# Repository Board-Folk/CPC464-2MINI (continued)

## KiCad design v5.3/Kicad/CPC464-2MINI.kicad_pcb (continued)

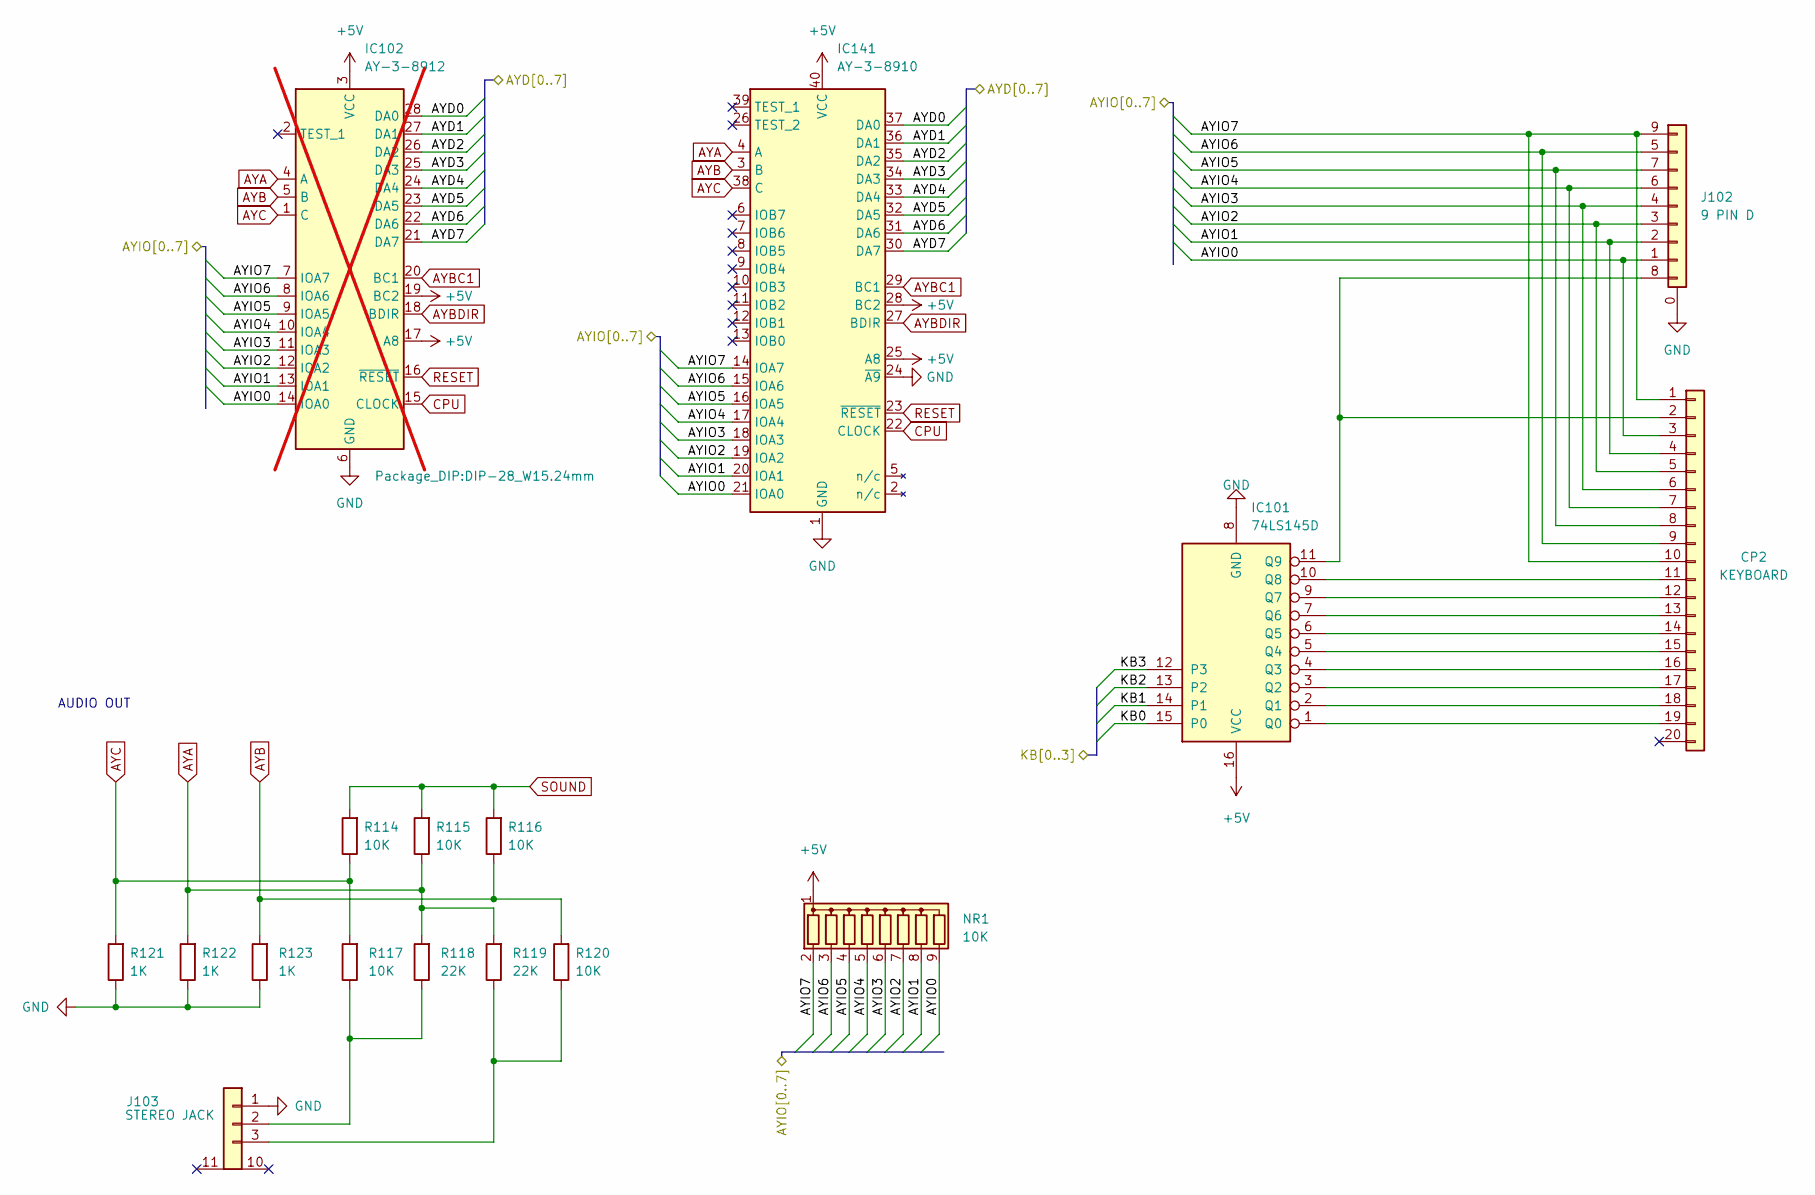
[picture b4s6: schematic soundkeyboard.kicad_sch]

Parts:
CP2: KEYBOARD; PinHeader_1x20_P2.54mm_Vertical
IC101: 74LS145D; SOIC-16_3.9x9.9mm_P1.27mm
IC102: AY-3-8912; DIP-28_W15.24mm; not fitted
IC141: AY-3-8910; DIP-40_W15.24mm
J102: 9 PIN D; DSUB-9_Male_Horizontal_P2.77x2.84mm_EdgePinOffset7.70mm_Hou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
J103: STEREO JACK; STEREO
NR1: 10K; R_Array_SIP9
R114, R115, R116, R117, R120: 10K; R_0805_2012Metric; LCSC C84376
R118, R119: 22K; R_0805_2012Metric; LCSC C114565
R121, R122, R123: 1K; R_0805_2012Metric; LCSC C482939

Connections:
+5V: IC101.16 (VCC), IC102.3 (VCC), IC102.17 (A8), IC102.19 (BC2), IC141.25 (A8), IC141.28 (BC2), IC141.40 (VCC), NR1.1 (common); also elsewhere on the board
/IO/AYD0: IC102.28 (DA0), IC141.37 (DA0); also elsewhere on the board
/IO/AYD1: IC102.27 (DA1), IC141.36 (DA1); also elsewhere on the board
/IO/AYD2: IC102.26 (DA2), IC141.35 (DA2); also elsewhere on the board
/IO/AYD3: IC102.25 (DA3), IC141.34 (DA3); also elsewhere on the board
/IO/AYD4: IC102.24 (DA4), IC141.33 (DA4); also elsewhere on the board
/IO/AYD5: IC102.23 (DA5), IC141.32 (DA5); also elsewhere on the board
/IO/AYD6: IC102.22 (DA6), IC141.31 (DA6); also elsewhere on the board
/IO/AYD7: IC102.21 (DA7), IC141.30 (DA7); also elsewhere on the board
/IO/KB0: IC101.15 (P0); also elsewhere on the board
/IO/KB1: IC101.14 (P1); also elsewhere on the board
/IO/KB2: IC101.13 (P2); also elsewhere on the board
/IO/KB3: IC101.12 (P3); also elsewhere on the board
/Sound & Keyboard/AYIO0: CP2.3, IC102.14 (IOA0), IC141.21 (IOA0), J102.1, NR1.9 (R8)
/Sound & Keyboard/AYIO1: CP2.4, IC102.13 (IOA1), IC141.20 (IOA1), J102.2, NR1.8 (R7)
/Sound & Keyboard/AYIO2: CP2.5, IC102.12 (IOA2), IC141.19 (IOA2), J102.3, NR1.7 (R6)
/Sound & Keyboard/AYIO3: CP2.6, IC102.11 (IOA3), IC141.18 (IOA3), J102.4, NR1.6 (R5)
/Sound & Keyboard/AYIO4: CP2.7, IC102.10 (IOA4), IC141.17 (IOA4), J102.6, NR1.5 (R4)
/Sound & Keyboard/AYIO5: CP2.8, IC102.9 (IOA5), IC141.16 (IOA5), J102.7, NR1.4 (R3)
/Sound & Keyboard/AYIO6: CP2.9, IC102.8 (IOA6), IC141.15 (IOA6), J102.5, NR1.3 (R2)
/Sound & Keyboard/AYIO7: CP2.1, CP2.10, IC102.7 (IOA7), IC141.14 (IOA7), J102.9, NR1.2 (R1)
AYA: IC102.4 (A), IC141.4 (A), R115.1, R118.2, R119.2, R122.2
AYB: IC102.5 (B), IC141.3 (B), R116.1, R120.2, R123.2
AYBC1: IC102.20 (BC1), IC141.29 (BC1); also elsewhere on the board
AYBDIR: IC102.18 (BDIR), IC141.27 (BDIR); also elsewhere on the board
AYC: IC102.1 (C), IC141.38 (C), R114.1, R117.2, R121.2
CPU: IC102.15 (CLOCK), IC141.22 (CLOCK); also elsewhere on the board
GND: IC101.8 (GND), IC102.6 (GND), IC141.1 (GND), IC141.24 (~A9), J102.0 (GND), J103.1, R121.1, R122.1, R123.1; also elsewhere on the board
unnamed: CP2.2, IC101.11 (Q9), J102.8
unnamed: CP2.11, IC101.10 (Q8)
unnamed: CP2.12, IC101.9 (Q7)
unnamed: CP2.13, IC101.7 (Q6)
unnamed: CP2.14, IC101.6 (Q5)
unnamed: CP2.15, IC101.5 (Q4)
unnamed: CP2.16, IC101.4 (Q3)
unnamed: CP2.17, IC101.3 (Q2)
unnamed: CP2.18, IC101.2 (Q1)
unnamed: CP2.19, IC101.1 (Q0)
unnamed: J103.3 (Ground), R119.1, R120.1
unnamed: J103.2, R117.1, R118.1
RESET: IC102.16 (~RESET), IC141.23 (~RESET); also elsewhere on the board
SOUND: R114.2, R115.2, R116.2; also elsewhere on the board

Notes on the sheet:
AUDIO OUT

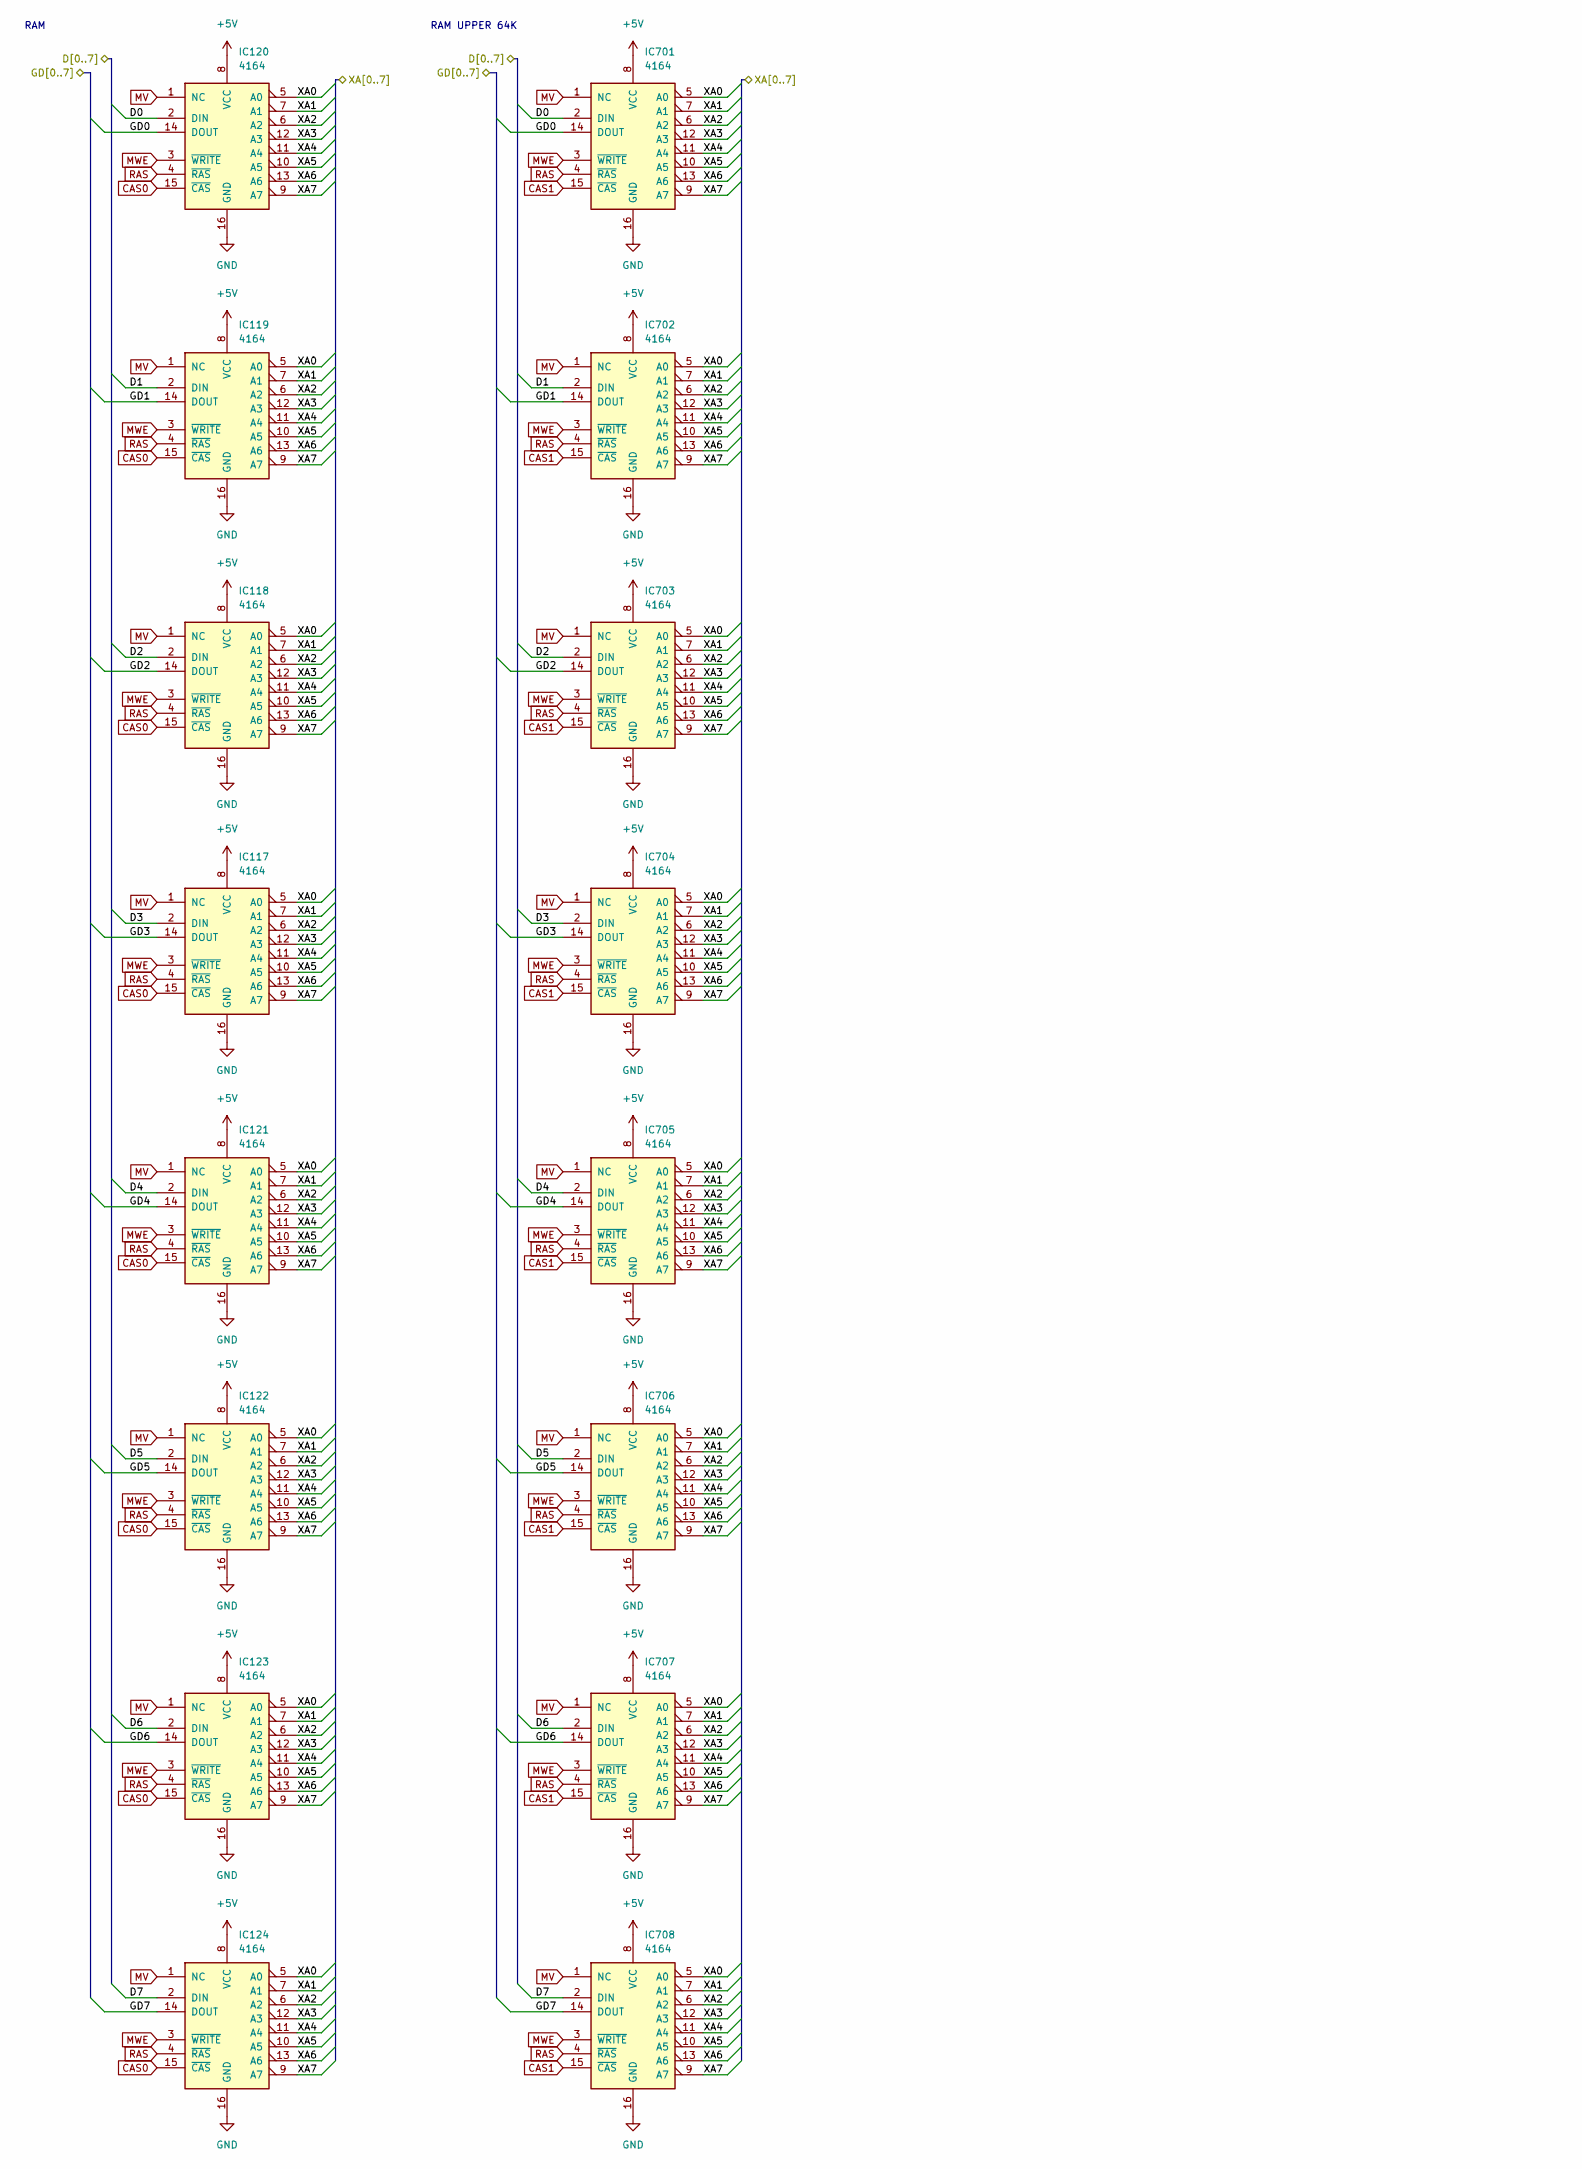
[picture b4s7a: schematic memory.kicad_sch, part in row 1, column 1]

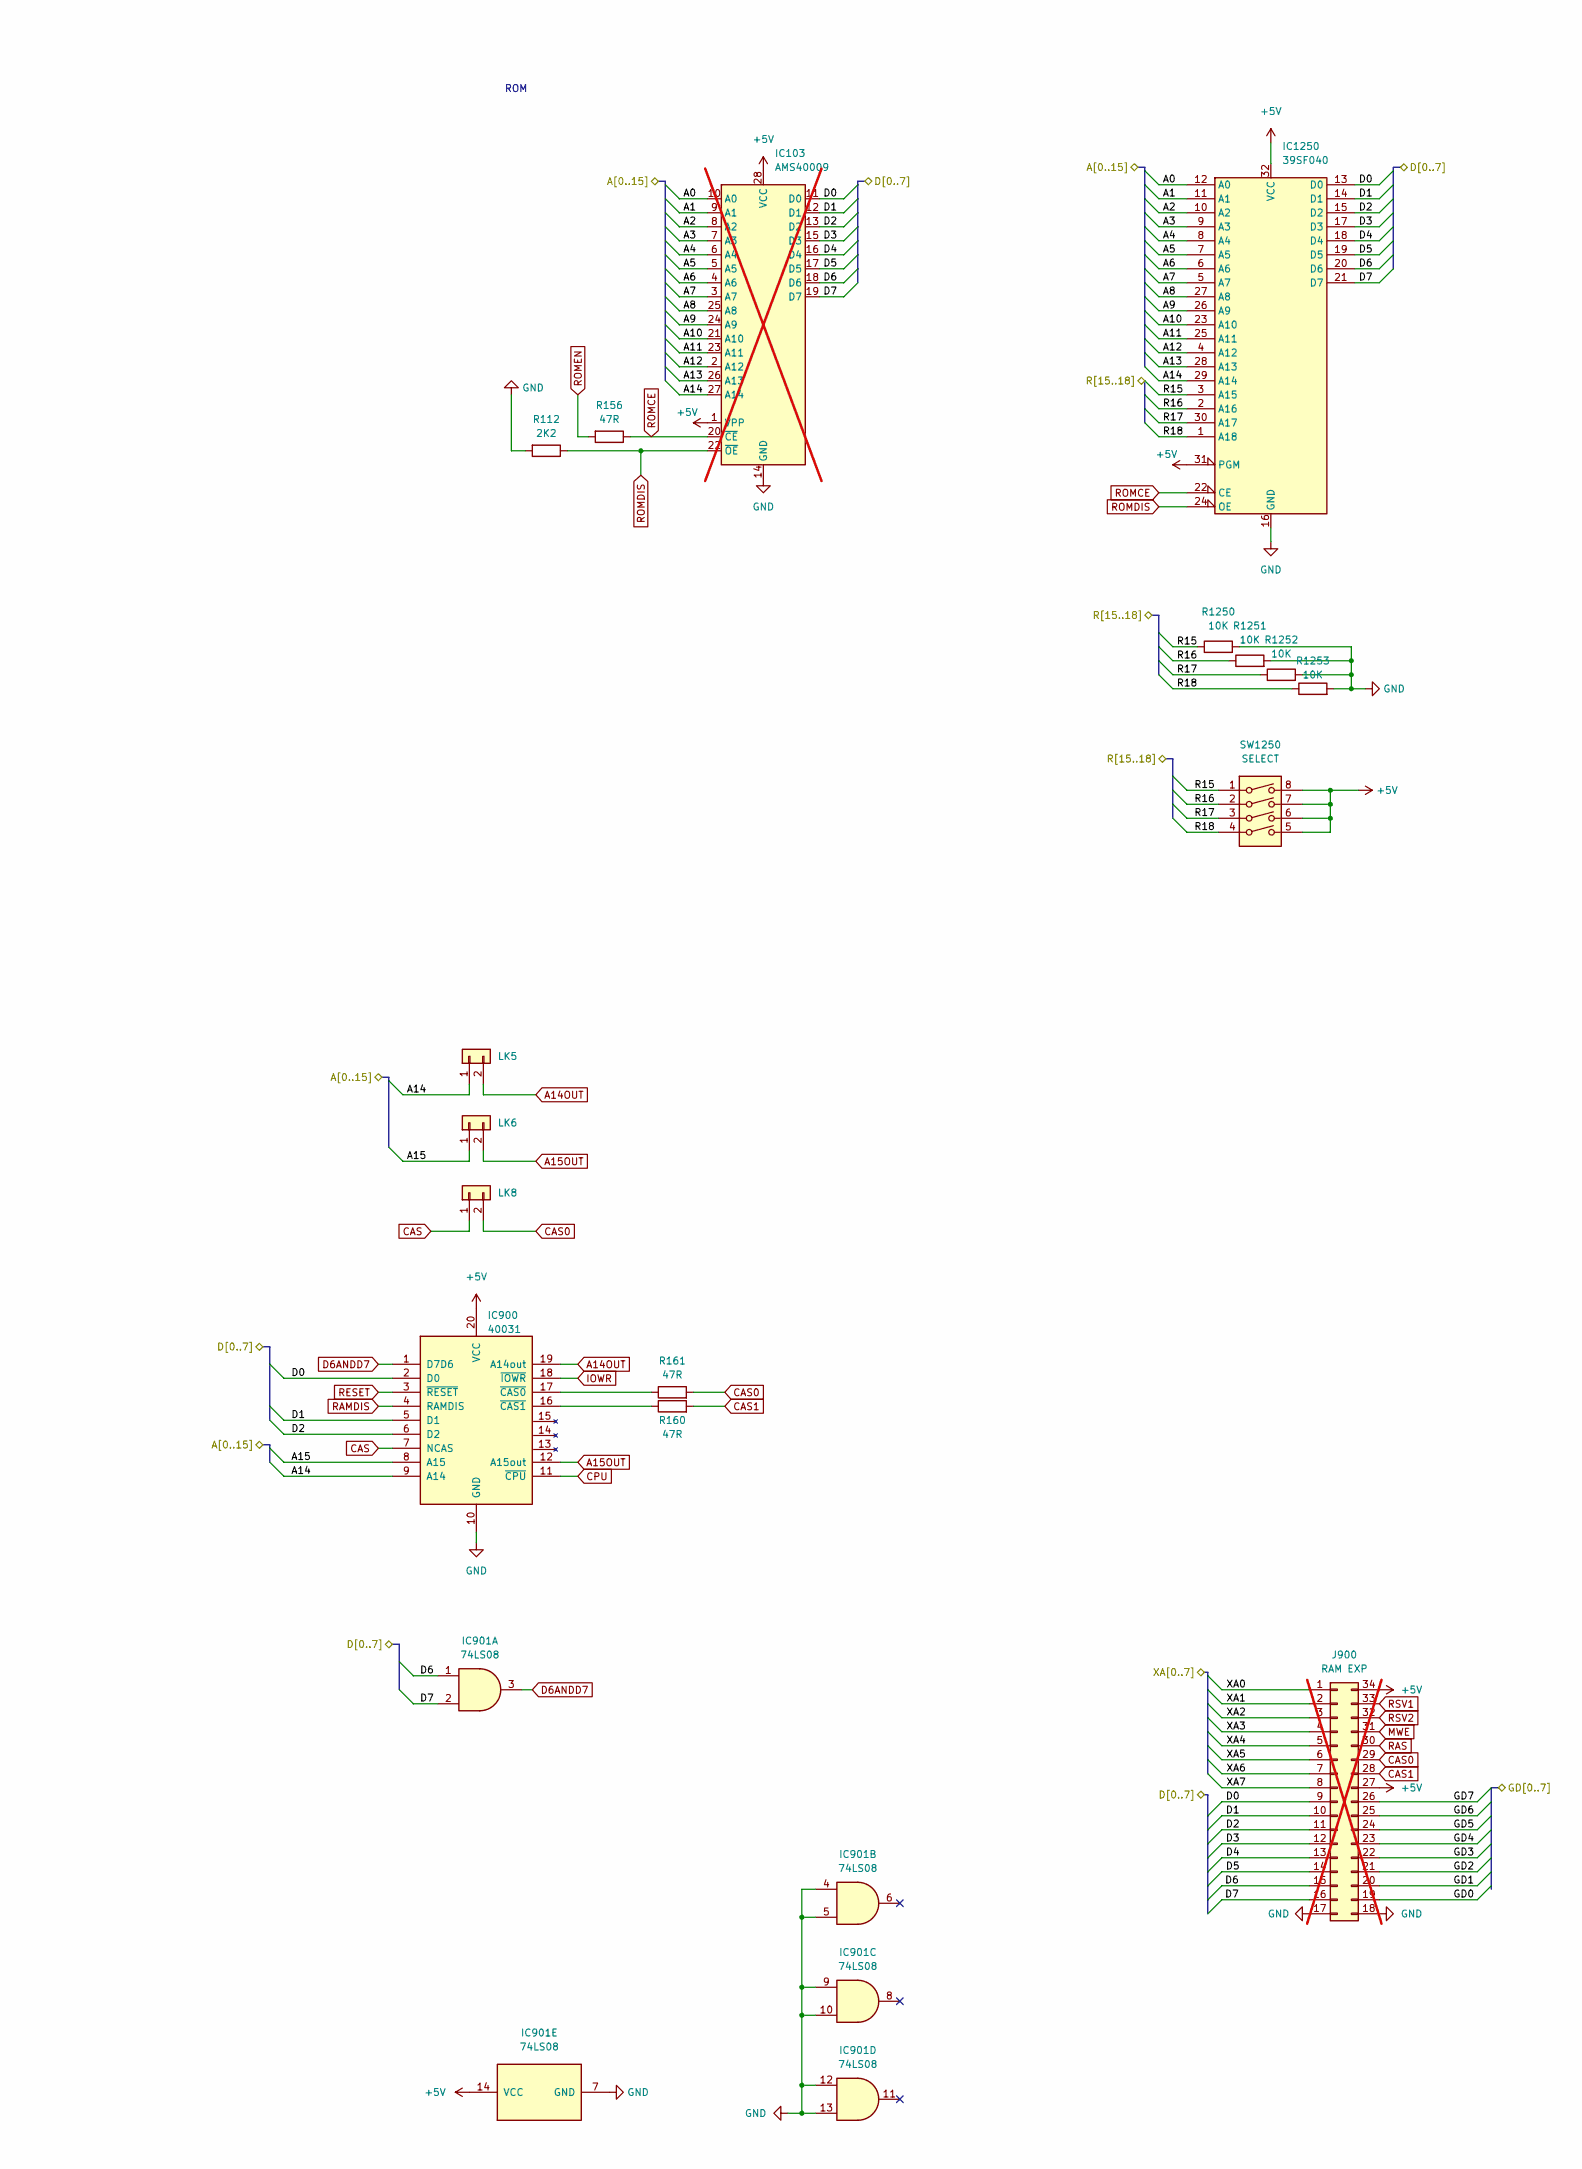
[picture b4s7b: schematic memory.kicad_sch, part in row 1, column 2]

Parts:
IC103: AMS40009; DIP-28_W15.24mm; not fitted
IC117, IC118, IC119, IC120, IC121, IC122, IC123, IC124, IC701, IC702, IC703, IC704, IC705, IC706, IC707, IC708: 4164; DIP-16_W7.62mm
IC900: 40031; SOIC-20W_7.5x12.8mm_P1.27mm
IC901: 74LS08; SOIC-14_3.9x8.7mm_P1.27mm
IC1250: 39SF040; PLCC-32_THT-Socket
J900: RAM EXP; PinHeader_2x17_P2.54mm_Vertical; not fitted
LK5: LK5; PinHeader_1x02_P1.00mm_Vertical
LK6: LK6; PinHeader_1x02_P1.00mm_Vertical
LK8: LK8; PinHeader_1x02_P1.00mm_Vertical
R112: 2K2; R_0805_2012Metric; LCSC C114561
R156: 47R; R_0805_2012Metric; LCSC C114541
R160, R161: 47R; R_0805_2012Metric; LCSC C114245
R1250, R1251, R1252, R1253: 10K; R_0805_2012Metric
SW1250: SELECT; DIP-8_W7.62mm_Socket

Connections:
+5V: IC103.1 (VPP), IC103.28 (VCC), IC117.8 (VCC), IC118.8 (VCC), IC119.8 (VCC), IC120.8 (VCC), IC121.8 (VCC), IC122.8 (VCC), IC123.8 (VCC), IC124.8 (VCC), IC701.8 (VCC), IC702.8 (VCC), IC703.8 (VCC), IC704.8 (VCC), IC705.8 (VCC), IC706.8 (VCC), IC707.8 (VCC), IC708.8 (VCC), IC900.20 (VCC), IC901.14 (VCC), IC1250.31 (PGM), IC1250.32 (VCC), J900.27, J900.34, SW1250.5, SW1250.6, SW1250.7, SW1250.8; also elsewhere on the board
/CPU/A0: IC103.10 (A0), IC1250.12 (A0); also elsewhere on the board
/CPU/A1: IC103.9 (A1), IC1250.11 (A1); also elsewhere on the board
/CPU/A2: IC103.8 (A2), IC1250.10 (A2); also elsewhere on the board
/CPU/A3: IC103.7 (A3), IC1250.9 (A3); also elsewhere on the board
/CPU/A4: IC103.6 (A4), IC1250.8 (A4); also elsewhere on the board
/CPU/A5: IC103.5 (A5), IC1250.7 (A5); also elsewhere on the board
/CPU/A6: IC103.4 (A6), IC1250.6 (A6); also elsewhere on the board
/CPU/A7: IC103.3 (A7), IC1250.5 (A7); also elsewhere on the board
/CPU/A8: IC103.25 (A8), IC1250.27 (A8); also elsewhere on the board
/CPU/A9: IC103.24 (A9), IC1250.26 (A9); also elsewhere on the board
/CPU/A10: IC103.21 (A10), IC1250.23 (A10); also elsewhere on the board
/CPU/A11: IC103.23 (A11), IC1250.25 (A11); also elsewhere on the board
/CPU/A12: IC103.2 (A12), IC1250.4 (A12); also elsewhere on the board
/CPU/A13: IC103.26 (A13), IC1250.28 (A13); also elsewhere on the board
/CPU/A14: IC103.27 (A14), IC900.9 (A14), IC1250.29 (A14), LK5.1; also elsewhere on the board
/CPU/A15: IC900.8 (A15), LK6.1; also elsewhere on the board
/CPU/D0: IC103.11 (D0), IC120.2 (DIN), IC701.2 (DIN), IC900.2 (D0), IC1250.13 (D0), J900.9; also elsewhere on the board
/CPU/D1: IC103.12 (D1), IC119.2 (DIN), IC702.2 (DIN), IC900.5 (D1), IC1250.14 (D1), J900.10; also elsewhere on the board
/CPU/D2: IC103.13 (D2), IC118.2 (DIN), IC703.2 (DIN), IC900.6 (D2), IC1250.15 (D2), J900.11; also elsewhere on the board
/CPU/D3: IC103.15 (D3), IC117.2 (DIN), IC704.2 (DIN), IC1250.17 (D3), J900.12; also elsewhere on the board
/CPU/D4: IC103.16 (D4), IC121.2 (DIN), IC705.2 (DIN), IC1250.18 (D4), J900.13; also elsewhere on the board
/CPU/D5: IC103.17 (D5), IC122.2 (DIN), IC706.2 (DIN), IC1250.19 (D5), J900.14; also elsewhere on the board
/CPU/D6: IC103.18 (D6), IC123.2 (DIN), IC707.2 (DIN), IC901.1, IC1250.20 (D6), J900.15; also elsewhere on the board
/CPU/D7: IC103.19 (D7), IC124.2 (DIN), IC708.2 (DIN), IC901.2, IC1250.21 (D7), J900.16; also elsewhere on the board
/Gate Arrays/GD0: IC120.14 (DOUT), IC701.14 (DOUT), J900.19; also elsewhere on the board
/Gate Arrays/GD1: IC119.14 (DOUT), IC702.14 (DOUT), J900.20; also elsewhere on the board
/Gate Arrays/GD2: IC118.14 (DOUT), IC703.14 (DOUT), J900.21; also elsewhere on the board
/Gate Arrays/GD3: IC117.14 (DOUT), IC704.14 (DOUT), J900.22; also elsewhere on the board
/Gate Arrays/GD4: IC121.14 (DOUT), IC705.14 (DOUT), J900.23; also elsewhere on the board
/Gate Arrays/GD5: IC122.14 (DOUT), IC706.14 (DOUT), J900.24; also elsewhere on the board
/Gate Arrays/GD6: IC123.14 (DOUT), IC707.14 (DOUT), J900.25; also elsewhere on the board
/Gate Arrays/GD7: IC124.14 (DOUT), IC708.14 (DOUT), J900.26; also elsewhere on the board
/Memory/R15: IC1250.3 (A15), R1250.1, SW1250.1
/Memory/R16: IC1250.2 (A16), R1251.1, SW1250.2
/Memory/R17: IC1250.30 (A17), R1252.1, SW1250.3
/Memory/R18: IC1250.1 (A18), R1253.1, SW1250.4
/Memory/XA0: IC117.5 (A0), IC118.5 (A0), IC119.5 (A0), IC120.5 (A0), IC121.5 (A0), IC122.5 (A0), IC123.5 (A0), IC124.5 (A0), IC701.5 (A0), IC702.5 (A0), IC703.5 (A0), IC704.5 (A0), IC705.5 (A0), IC706.5 (A0), IC707.5 (A0), IC708.5 (A0), J900.1; also elsewhere on the board
/Memory/XA1: IC117.7 (A1), IC118.7 (A1), IC119.7 (A1), IC120.7 (A1), IC121.7 (A1), IC122.7 (A1), IC123.7 (A1), IC124.7 (A1), IC701.7 (A1), IC702.7 (A1), IC703.7 (A1), IC704.7 (A1), IC705.7 (A1), IC706.7 (A1), IC707.7 (A1), IC708.7 (A1), J900.2; also elsewhere on the board
/Memory/XA2: IC117.6 (A2), IC118.6 (A2), IC119.6 (A2), IC120.6 (A2), IC121.6 (A2), IC122.6 (A2), IC123.6 (A2), IC124.6 (A2), IC701.6 (A2), IC702.6 (A2), IC703.6 (A2), IC704.6 (A2), IC705.6 (A2), IC706.6 (A2), IC707.6 (A2), IC708.6 (A2), J900.3; also elsewhere on the board
/Memory/XA3: IC117.12 (A3), IC118.12 (A3), IC119.12 (A3), IC120.12 (A3), IC121.12 (A3), IC122.12 (A3), IC123.12 (A3), IC124.12 (A3), IC701.12 (A3), IC702.12 (A3), IC703.12 (A3), IC704.12 (A3), IC705.12 (A3), IC706.12 (A3), IC707.12 (A3), IC708.12 (A3), J900.4; also elsewhere on the board
/Memory/XA4: IC117.11 (A4), IC118.11 (A4), IC119.11 (A4), IC120.11 (A4), IC121.11 (A4), IC122.11 (A4), IC123.11 (A4), IC124.11 (A4), IC701.11 (A4), IC702.11 (A4), IC703.11 (A4), IC704.11 (A4), IC705.11 (A4), IC706.11 (A4), IC707.11 (A4), IC708.11 (A4), J900.5; also elsewhere on the board
/Memory/XA5: IC117.10 (A5), IC118.10 (A5), IC119.10 (A5), IC120.10 (A5), IC121.10 (A5), IC122.10 (A5), IC123.10 (A5), IC124.10 (A5), IC701.10 (A5), IC702.10 (A5), IC703.10 (A5), IC704.10 (A5), IC705.10 (A5), IC706.10 (A5), IC707.10 (A5), IC708.10 (A5), J900.6; also elsewhere on the board
/Memory/XA6: IC117.13 (A6), IC118.13 (A6), IC119.13 (A6), IC120.13 (A6), IC121.13 (A6), IC122.13 (A6), IC123.13 (A6), IC124.13 (A6), IC701.13 (A6), IC702.13 (A6), IC703.13 (A6), IC704.13 (A6), IC705.13 (A6), IC706.13 (A6), IC707.13 (A6), IC708.13 (A6), J900.7; also elsewhere on the board
/Memory/XA7: IC117.9 (A7), IC118.9 (A7), IC119.9 (A7), IC120.9 (A7), IC121.9 (A7), IC122.9 (A7), IC123.9 (A7), IC124.9 (A7), IC701.9 (A7), IC702.9 (A7), IC703.9 (A7), IC704.9 (A7), IC705.9 (A7), IC706.9 (A7), IC707.9 (A7), IC708.9 (A7), J900.8; also elsewhere on the board
A14OUT: IC900.19 (A14out), LK5.2; also elsewhere on the board
A15OUT: IC900.12 (A15out), LK6.2; also elsewhere on the board
CAS: IC900.7 (NCAS), LK8.1; also elsewhere on the board
CAS0: IC117.15 (~CAS), IC118.15 (~CAS), IC119.15 (~CAS), IC120.15 (~CAS), IC121.15 (~CAS), IC122.15 (~CAS), IC123.15 (~CAS), IC124.15 (~CAS), J900.29, LK8.2, R161.2
CAS1: IC701.15 (~CAS), IC702.15 (~CAS), IC703.15 (~CAS), IC704.15 (~CAS), IC705.15 (~CAS), IC706.15 (~CAS), IC707.15 (~CAS), IC708.15 (~CAS), J900.28, R160.2
CPU: IC900.11 (~CPU); also elsewhere on the board
D6ANDD7: IC900.1 (D7D6), IC901.3
GND: IC103.14 (GND), IC117.16 (GND), IC118.16 (GND), IC119.16 (GND), IC120.16 (GND), IC121.16 (GND), IC122.16 (GND), IC123.16 (GND), IC124.16 (GND), IC701.16 (GND), IC702.16 (GND), IC703.16 (GND), IC704.16 (GND), IC705.16 (GND), IC706.16 (GND), IC707.16 (GND), IC708.16 (GND), IC900.10 (GND), IC901.4, IC901.5, IC901.7 (GND), IC901.9, IC901.10, IC901.12, IC901.13, IC1250.16 (GND), J900.17, J900.18, R112.2, R1250.2, R1251.2, R1252.2, R1253.2; also elsewhere on the board
IOWR: IC900.18 (~IOWR); also elsewhere on the board
MV: IC117.1 (NC), IC118.1 (NC), IC119.1 (NC), IC120.1 (NC), IC121.1 (NC), IC122.1 (NC), IC123.1 (NC), IC124.1 (NC), IC701.1 (NC), IC702.1 (NC), IC703.1 (NC), IC704.1 (NC), IC705.1 (NC), IC706.1 (NC), IC707.1 (NC), IC708.1 (NC)
MWE: IC117.3 (~WRITE), IC118.3 (~WRITE), IC119.3 (~WRITE), IC120.3 (~WRITE), IC121.3 (~WRITE), IC122.3 (~WRITE), IC123.3 (~WRITE), IC124.3 (~WRITE), IC701.3 (~WRITE), IC702.3 (~WRITE), IC703.3 (~WRITE), IC704.3 (~WRITE), IC705.3 (~WRITE), IC706.3 (~WRITE), IC707.3 (~WRITE), IC708.3 (~WRITE), J900.31; also elsewhere on the board
unnamed: IC900.17 (~CAS0), R161.1
unnamed: IC900.16 (~CAS1), R160.1
RAMDIS: IC900.4 (RAMDIS); also elsewhere on the board
RAS: IC117.4 (~RAS), IC118.4 (~RAS), IC119.4 (~RAS), IC120.4 (~RAS), IC121.4 (~RAS), IC122.4 (~RAS), IC123.4 (~RAS), IC124.4 (~RAS), IC701.4 (~RAS), IC702.4 (~RAS), IC703.4 (~RAS), IC704.4 (~RAS), IC705.4 (~RAS), IC706.4 (~RAS), IC707.4 (~RAS), IC708.4 (~RAS), J900.30; also elsewhere on the board
RESET: IC900.3 (~RESET); also elsewhere on the board
ROMCE: IC103.20 (~CE), IC1250.22 (CE), R156.1
ROMDIS: IC103.22 (~OE), IC1250.24 (OE), R112.1; also elsewhere on the board
ROMEN: R156.2; also elsewhere on the board

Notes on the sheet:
RAM UPPER 64K
RAM
ROM

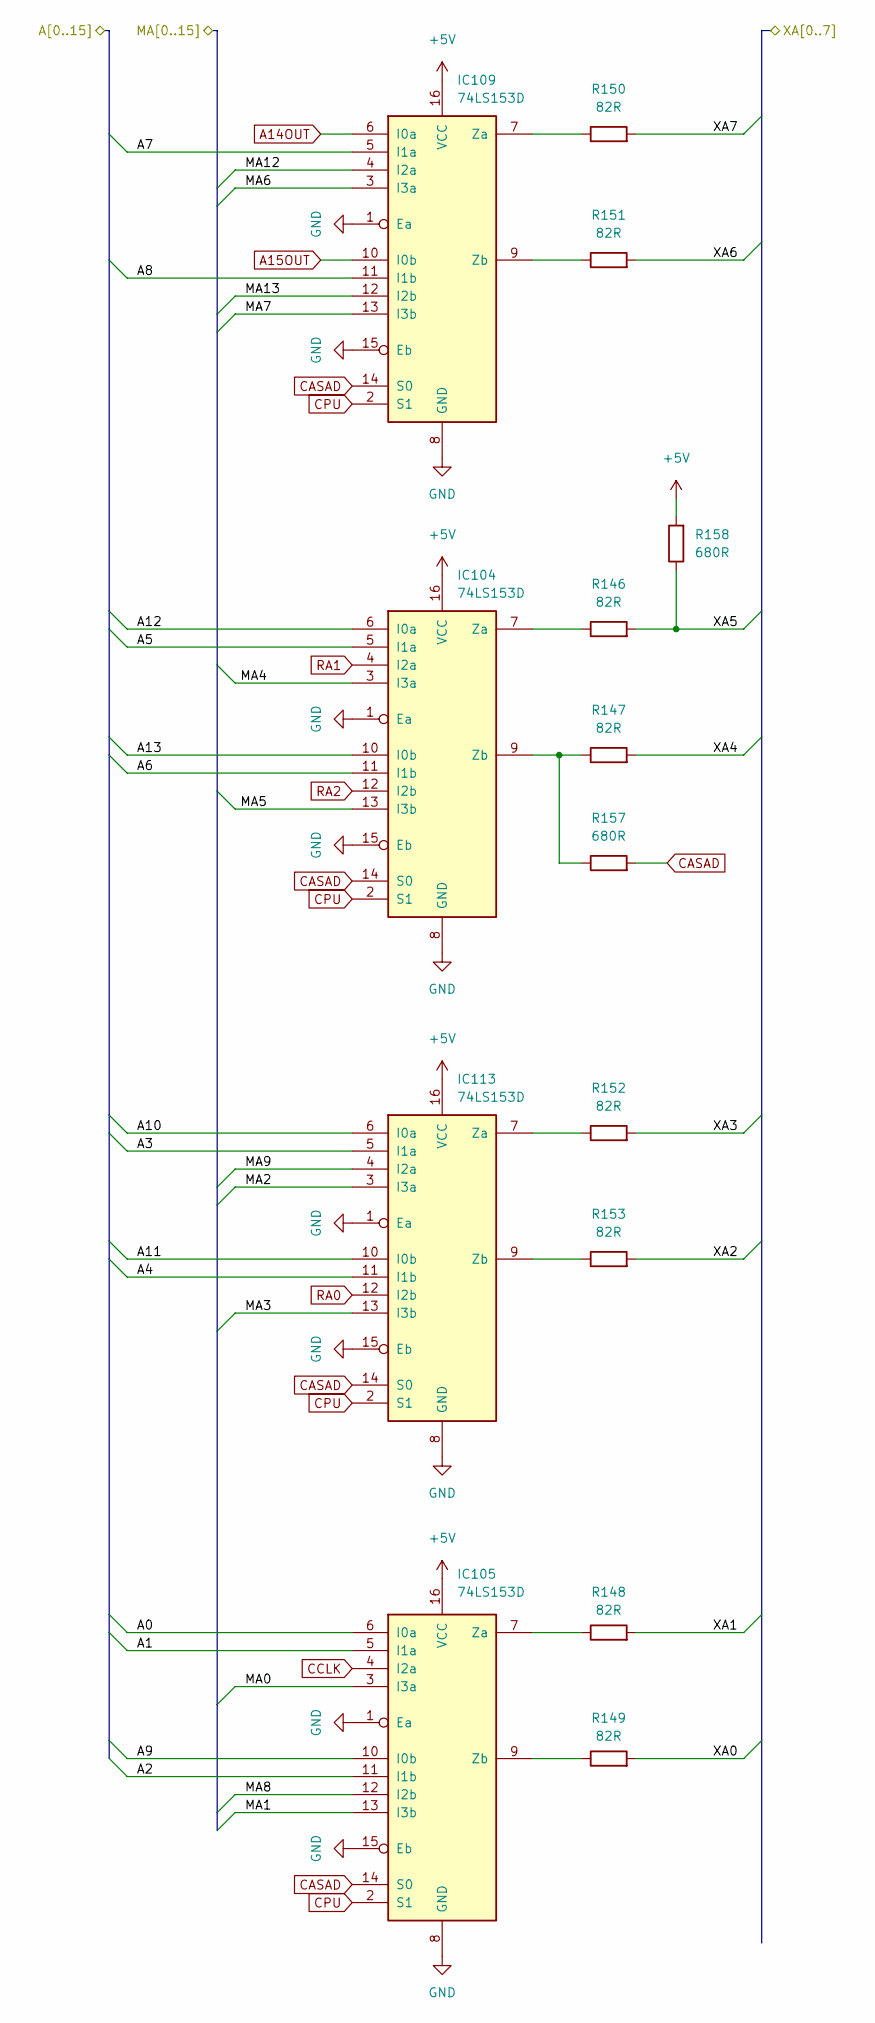
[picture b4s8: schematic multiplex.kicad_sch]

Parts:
IC104, IC105, IC109, IC113: 74LS153D; SOIC-16_3.9x9.9mm_P1.27mm
R146, R147, R148, R149, R150, R151, R152, R153: 82R; R_0805_2012Metric; LCSC C114245
R157, R158: 680R; R_0805_2012Metric; LCSC C114549

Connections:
+5V: IC104.16 (VCC), IC105.16 (VCC), IC109.16 (VCC), IC113.16 (VCC), R158.2; also elsewhere on the board
/CPU/A0: IC105.6 (I0a); also elsewhere on the board
/CPU/A1: IC105.5 (I1a); also elsewhere on the board
/CPU/A2: IC105.11 (I1b); also elsewhere on the board
/CPU/A3: IC113.5 (I1a); also elsewhere on the board
/CPU/A4: IC113.11 (I1b); also elsewhere on the board
/CPU/A5: IC104.5 (I1a); also elsewhere on the board
/CPU/A6: IC104.11 (I1b); also elsewhere on the board
/CPU/A7: IC109.5 (I1a); also elsewhere on the board
/CPU/A8: IC109.11 (I1b); also elsewhere on the board
/CPU/A9: IC105.10 (I0b); also elsewhere on the board
/CPU/A10: IC113.6 (I0a); also elsewhere on the board
/CPU/A11: IC113.10 (I0b); also elsewhere on the board
/CPU/A12: IC104.6 (I0a); also elsewhere on the board
/CPU/A13: IC104.10 (I0b); also elsewhere on the board
/Memory/XA0: R149.2; also elsewhere on the board
/Memory/XA1: R148.2; also elsewhere on the board
/Memory/XA2: R153.2; also elsewhere on the board
/Memory/XA3: R152.2; also elsewhere on the board
/Memory/XA4: R147.2; also elsewhere on the board
/Memory/XA5: R146.2, R158.1; also elsewhere on the board
/Memory/XA6: R151.2; also elsewhere on the board
/Memory/XA7: R150.2; also elsewhere on the board
/Multiplex/MA0: IC105.3 (I3a); also elsewhere on the board
/Multiplex/MA1: IC105.13 (I3b); also elsewhere on the board
/Multiplex/MA2: IC113.3 (I3a); also elsewhere on the board
/Multiplex/MA3: IC113.13 (I3b); also elsewhere on the board
/Multiplex/MA4: IC104.3 (I3a); also elsewhere on the board
/Multiplex/MA5: IC104.13 (I3b); also elsewhere on the board
/Multiplex/MA6: IC109.3 (I3a); also elsewhere on the board
/Multiplex/MA7: IC109.13 (I3b); also elsewhere on the board
/Multiplex/MA8: IC105.12 (I2b); also elsewhere on the board
/Multiplex/MA9: IC113.4 (I2a); also elsewhere on the board
/Multiplex/MA12: IC109.4 (I2a); also elsewhere on the board
/Multiplex/MA13: IC109.12 (I2b); also elsewhere on the board
A14OUT: IC109.6 (I0a); also elsewhere on the board
A15OUT: IC109.10 (I0b); also elsewhere on the board
CASAD: IC104.14 (S0), IC105.14 (S0), IC109.14 (S0), IC113.14 (S0), R157.2; also elsewhere on the board
CCLK: IC105.4 (I2a); also elsewhere on the board
CPU: IC104.2 (S1), IC105.2 (S1), IC109.2 (S1), IC113.2 (S1); also elsewhere on the board
GND: IC104.1 (Ea), IC104.8 (GND), IC104.15 (Eb), IC105.1 (Ea), IC105.8 (GND), IC105.15 (Eb), IC109.1 (Ea), IC109.8 (GND), IC109.15 (Eb), IC113.1 (Ea), IC113.8 (GND), IC113.15 (Eb); also elsewhere on the board
unnamed: IC104.7 (Za), R146.1
unnamed: IC104.9 (Zb), R147.1, R157.1
unnamed: IC105.7 (Za), R148.1
unnamed: IC105.9 (Zb), R149.1
unnamed: IC109.7 (Za), R150.1
unnamed: IC109.9 (Zb), R151.1
unnamed: IC113.7 (Za), R152.1
unnamed: IC113.9 (Zb), R153.1
RA0: IC113.12 (I2b); also elsewhere on the board
RA1: IC104.4 (I2a); also elsewhere on the board
RA2: IC104.12 (I2b); also elsewhere on the board

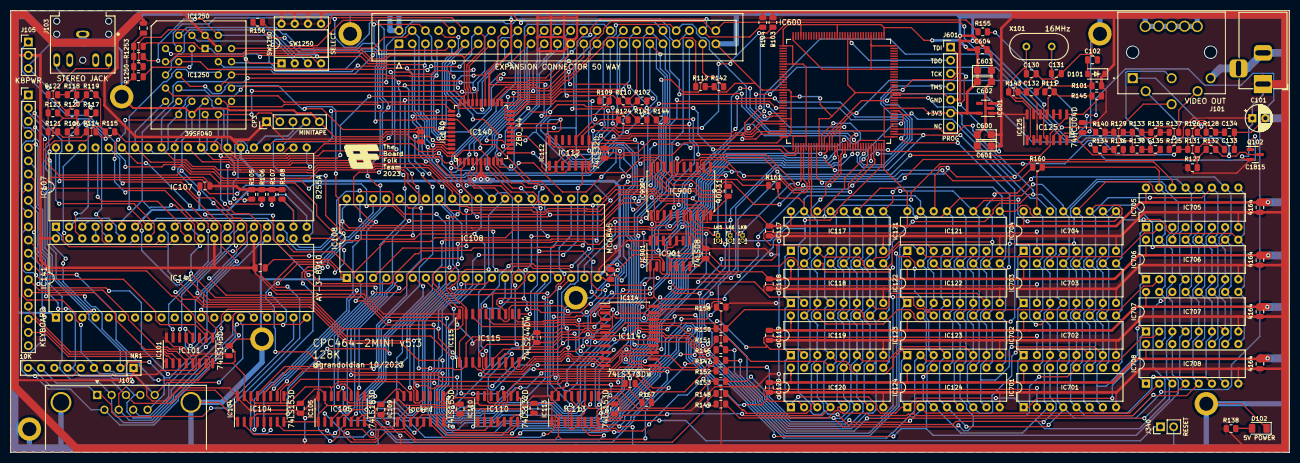
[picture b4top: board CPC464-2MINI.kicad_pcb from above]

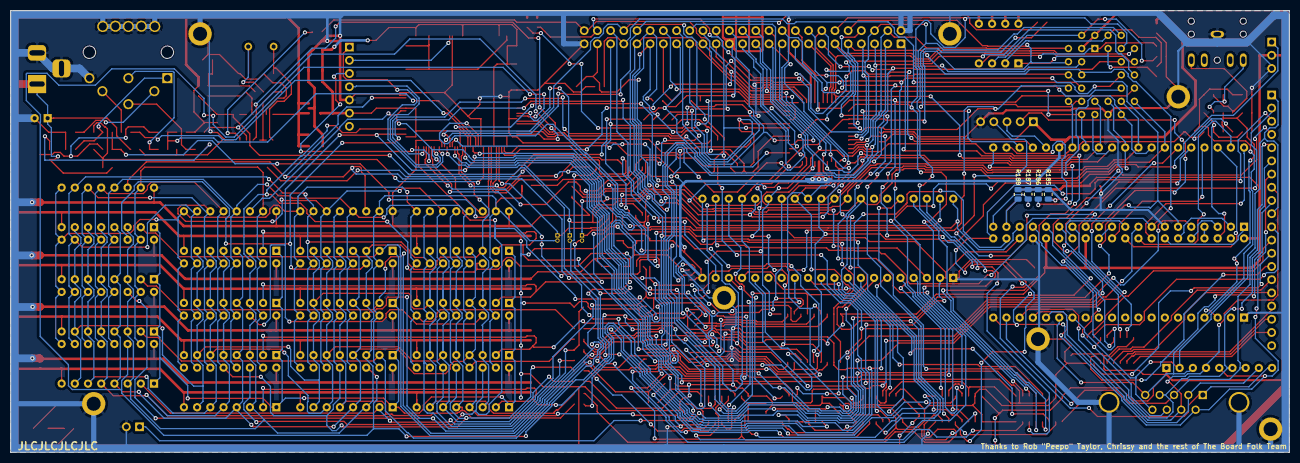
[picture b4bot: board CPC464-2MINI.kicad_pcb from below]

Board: 2 copper layers, 246.0 x 85.0 mm, 164 parts (4 on the bottom side), 190 nets.
